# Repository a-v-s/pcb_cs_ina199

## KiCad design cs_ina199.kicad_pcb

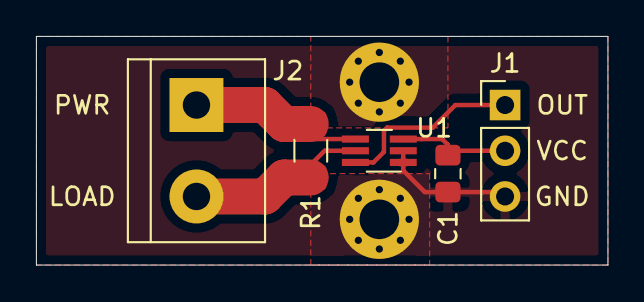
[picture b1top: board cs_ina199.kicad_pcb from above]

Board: 2 copper layers, 31.7 x 12.7 mm, 7 parts (0 on the bottom side), 5 nets.

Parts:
C1: C_Small; C_0805_2012Metric_Pad1.15x1.40mm_HandSolder
H1, H2: MountingHole; MountingHole_2.2mm_M2_Pad_Via
J1: Conn_01x03; PinHeader_1x03_P2.54mm_Vertical
J2: Conn_01x02; TerminalBlock_bornier-2_P5.08mm
R1: R_Small; R_1206_3216Metric_Pad1.42x1.75mm_HandSolder
U1: INA199; SOT-363_SC-70-6_Handsoldering

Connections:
GND: C1.2, H1.1, H2.1, J1.3, U1.1, U1.2
unnamed: J2.1, R1.1, U1.4
unnamed: J2.2, R1.2, U1.5
OUT: J1.1, U1.6
VCC: C1.1, J1.2, U1.3

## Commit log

2020-01-04 INA199 Breakout v1.0
